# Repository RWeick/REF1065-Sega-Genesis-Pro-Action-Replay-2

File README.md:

# REF1065-Sega-Genesis-Pro-Action-Replay-2
The Kicad files and eprom dump of the Sega Genesis Pro Action Replay 2.

PCB Thickness: 1.6 mm

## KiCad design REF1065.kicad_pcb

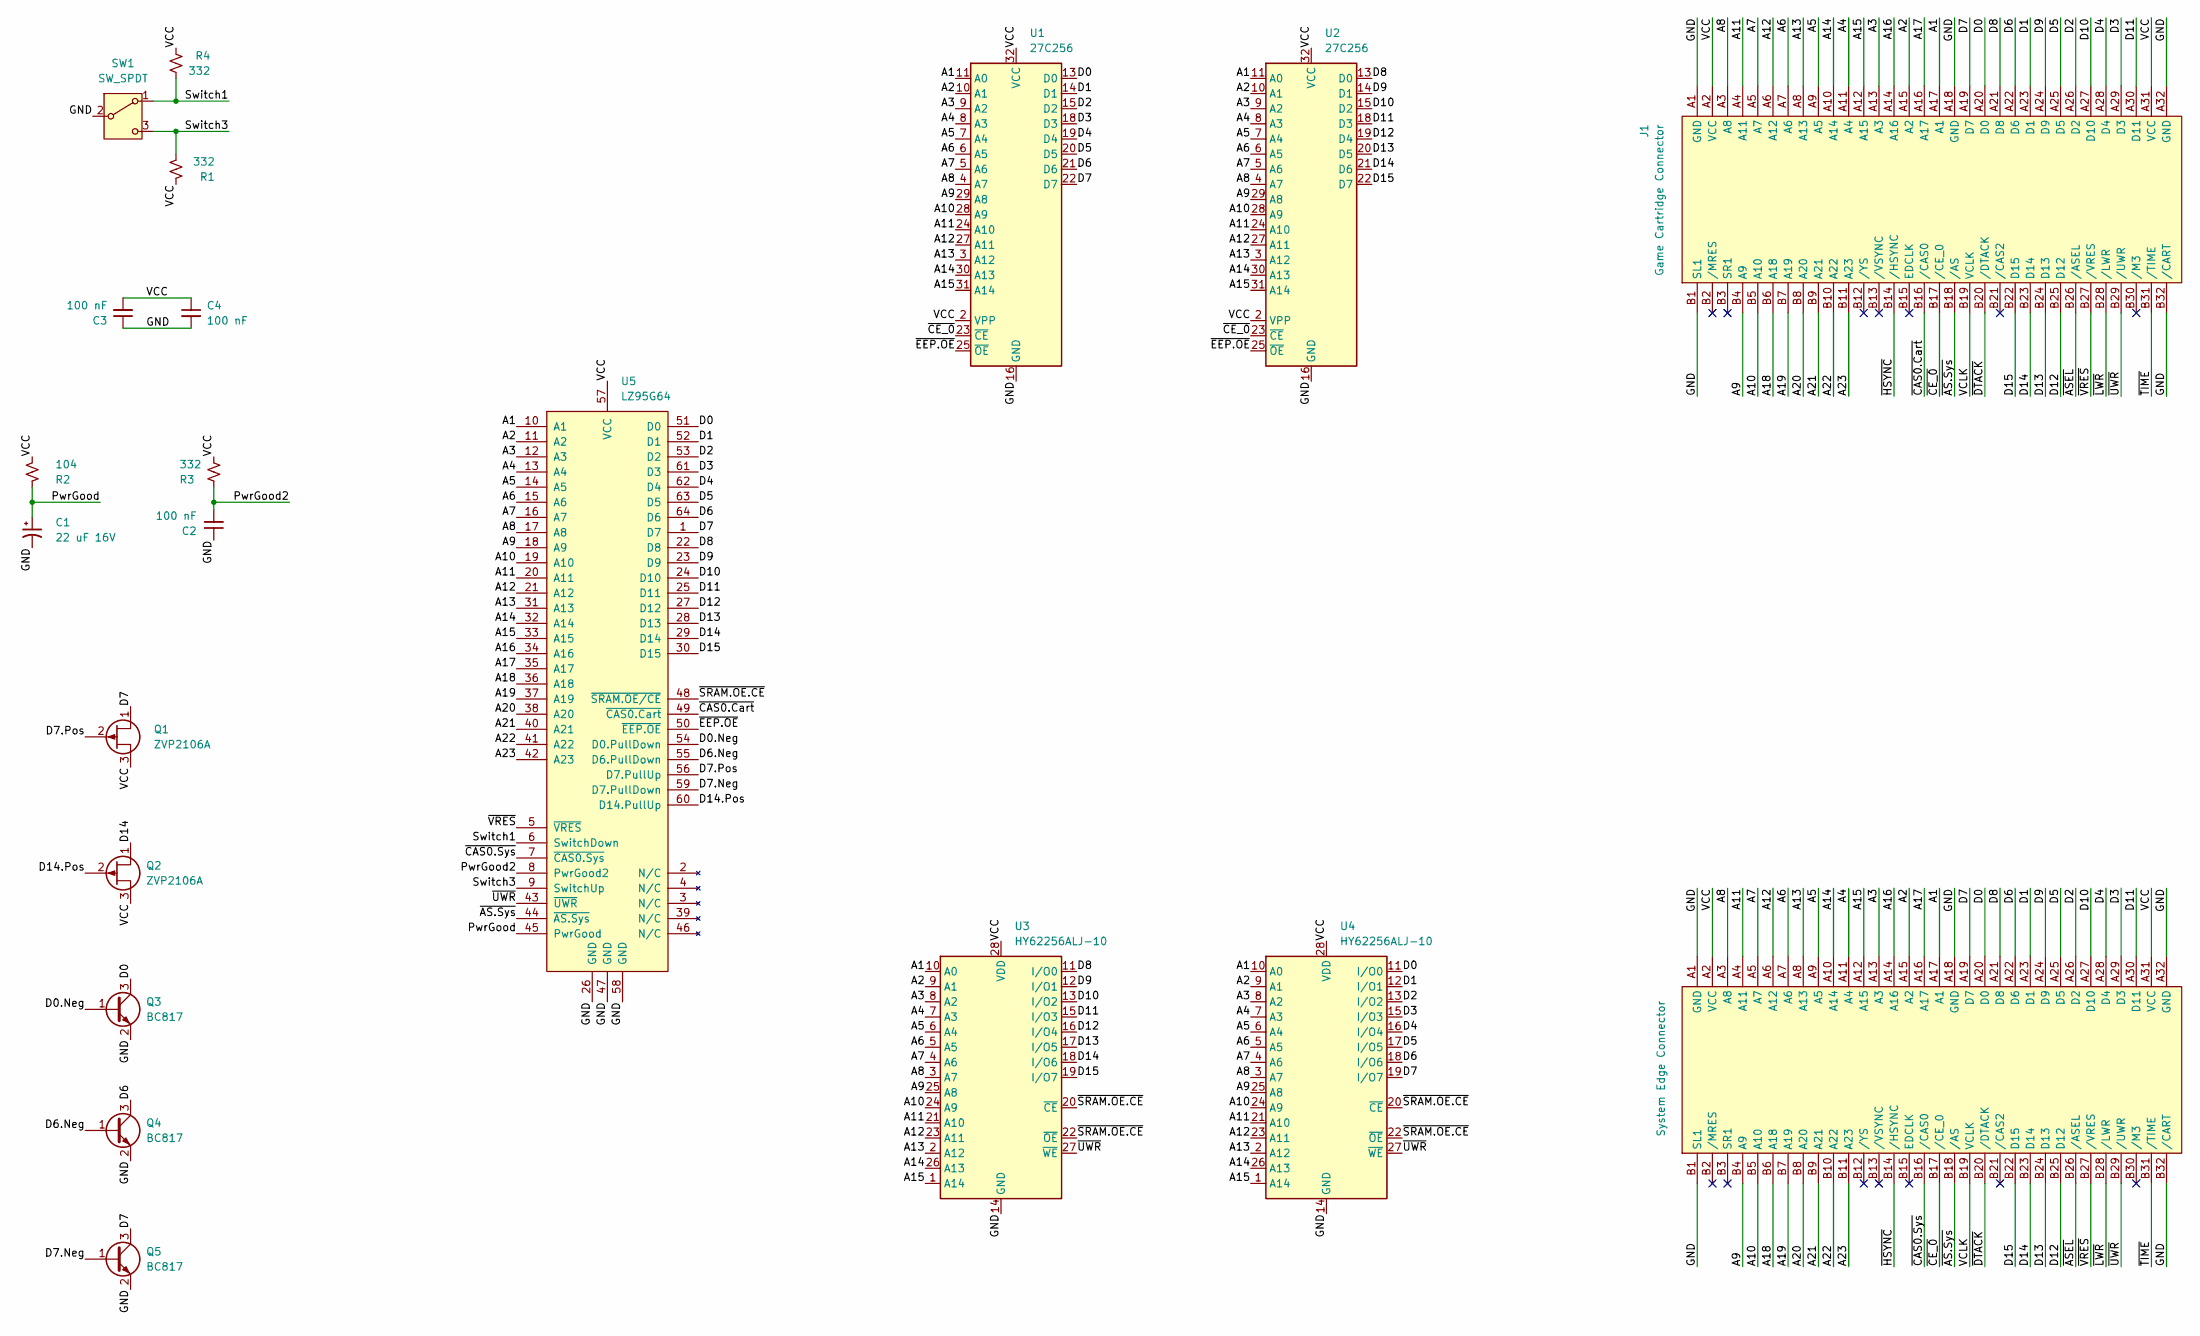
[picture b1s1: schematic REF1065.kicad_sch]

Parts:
C1: 22 uF 16V; Capacitor
C2, C3, C4: 100 nF; Capacitor
J1: Game Cartridge Connector; Upper Edge Connector
J2: System Edge Connector; Lower Edge Connector
Q1, Q2: ZVP2106A; TO-92Flat
Q3, Q4, Q5: BC817; SOT-23
R1, R3, R4: 332; Resistor
R2: 104; Resistor
SW1: SW_SPDT; Switch
U1, U2: 27C256
U3, U4: HY62256ALJ-10; HY62256ALJ
U5: LZ95G64

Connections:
/A1: J1.A17 (A1), J2.A17 (A1), U1.11 (A0), U2.11 (A0), U3.10 (A0), U4.10 (A0), U5.10 (A1)
/A2: J1.A15 (A2), J2.A15 (A2), U1.10 (A1), U2.10 (A1), U3.9 (A1), U4.9 (A1), U5.11 (A2)
/A3: J1.A13 (A3), J2.A13 (A3), U1.9 (A2), U2.9 (A2), U3.8 (A2), U4.8 (A2), U5.12 (A3)
/A4: J1.A11 (A4), J2.A11 (A4), U1.8 (A3), U2.8 (A3), U3.7 (A3), U4.7 (A3), U5.13 (A4)
/A5: J1.A9 (A5), J2.A9 (A5), U1.7 (A4), U2.7 (A4), U3.6 (A4), U4.6 (A4), U5.14 (A5)
/A6: J1.A7 (A6), J2.A7 (A6), U1.6 (A5), U2.6 (A5), U3.5 (A5), U4.5 (A5), U5.15 (A6)
/A7: J1.A5 (A7), J2.A5 (A7), U1.5 (A6), U2.5 (A6), U3.4 (A6), U4.4 (A6), U5.16 (A7)
/A8: J1.A3 (A8), J2.A3 (A8), U1.4 (A7), U2.4 (A7), U3.3 (A7), U4.3 (A7), U5.17 (A8)
/A9: J1.B4 (A9), J2.B4 (A9), U1.29 (A8), U2.29 (A8), U3.25 (A8), U4.25 (A8), U5.18 (A9)
/A10: J1.B5 (A10), J2.B5 (A10), U1.28 (A9), U2.28 (A9), U3.24 (A9), U4.24 (A9), U5.19 (A10)
/A11: J1.A4 (A11), J2.A4 (A11), U1.24 (A10), U2.24 (A10), U3.21 (A10), U4.21 (A10), U5.20 (A11)
/A12: J1.A6 (A12), J2.A6 (A12), U1.27 (A11), U2.27 (A11), U3.23 (A11), U4.23 (A11), U5.21 (A12)
/A13: J1.A8 (A13), J2.A8 (A13), U1.3 (A12), U2.3 (A12), U3.2 (A12), U4.2 (A12), U5.31 (A13)
/A14: J1.A10 (A14), J2.A10 (A14), U1.30 (A13), U2.30 (A13), U3.26 (A13), U4.26 (A13), U5.32 (A14)
/A15: J1.A12 (A15), J2.A12 (A15), U1.31 (A14), U2.31 (A14), U3.1 (A14), U4.1 (A14), U5.33 (A15)
/A16: J1.A14 (A16), J2.A14 (A16), U5.34 (A16)
/A17: J1.A16 (A17), J2.A16 (A17), U5.35 (A17)
/A18: J1.B6 (A18), J2.B6 (A18), U5.36 (A18)
/A19: J1.B7 (A19), J2.B7 (A19), U5.37 (A19)
/A20: J1.B8 (A20), J2.B8 (A20), U5.38 (A20)
/A21: J1.B9 (A21), J2.B9 (A21), U5.40 (A21)
/A22: J1.B10 (A22), J2.B10 (A22), U5.41 (A22)
/A23: J1.B11 (A23), J2.B11 (A23), U5.42 (A23)
/D0: J1.A20 (D0), J2.A20 (D0), Q3.3 (C), U1.13 (D0), U4.11 (I/O0), U5.51 (D0)
/D0.Neg: Q3.1 (B), U5.54 (D0.PullDown)
/D1: J1.A23 (D1), J2.A23 (D1), U1.14 (D1), U4.12 (I/O1), U5.52 (D1)
/D2: J1.A26 (D2), J2.A26 (D2), U1.15 (D2), U4.13 (I/O2), U5.53 (D2)
/D3: J1.A29 (D3), J2.A29 (D3), U1.18 (D3), U4.15 (I/O3), U5.61 (D3)
/D4: J1.A28 (D4), J2.A28 (D4), U1.19 (D4), U4.16 (I/O4), U5.62 (D4)
/D5: J1.A25 (D5), J2.A25 (D5), U1.20 (D5), U4.17 (I/O5), U5.63 (D5)
/D6: J1.A22 (D6), J2.A22 (D6), Q4.3 (C), U1.21 (D6), U4.18 (I/O6), U5.64 (D6)
/D6.Neg: Q4.1 (B), U5.55 (D6.PullDown)
/D7: J1.A19 (D7), J2.A19 (D7), Q1.1 (D), Q5.3 (C), U1.22 (D7), U4.19 (I/O7), U5.1 (D7)
/D7.Neg: Q5.1 (B), U5.59 (D7.PullDown)
/D7.Pos: Q1.2 (G), U5.56 (D7.PullUp)
/D8: J1.A21 (D8), J2.A21 (D8), U2.13 (D0), U3.11 (I/O0), U5.22 (D8)
/D9: J1.A24 (D9), J2.A24 (D9), U2.14 (D1), U3.12 (I/O1), U5.23 (D9)
/D10: J1.A27 (D10), J2.A27 (D10), U2.15 (D2), U3.13 (I/O2), U5.24 (D10)
/D11: J1.A30 (D11), J2.A30 (D11), U2.18 (D3), U3.15 (I/O3), U5.25 (D11)
/D12: J1.B25 (D12), J2.B25 (D12), U2.19 (D4), U3.16 (I/O4), U5.27 (D12)
/D13: J1.B24 (D13), J2.B24 (D13), U2.20 (D5), U3.17 (I/O5), U5.28 (D13)
/D14: J1.B23 (D14), J2.B23 (D14), Q2.1 (D), U2.21 (D6), U3.18 (I/O6), U5.29 (D14)
/D14.Pos: Q2.2 (G), U5.60 (D14.PullUp)
/D15: J1.B22 (D15), J2.B22 (D15), U2.22 (D7), U3.19 (I/O7), U5.30 (D15)
/GND: C1.2, C2.1, C3.1, C4.2, J1.A1 (GND), J1.A18 (GND), J1.A32 (GND), J1.B1 (SL1), J1.B32 (/CART), J2.A1 (GND), J2.A18 (GND), J2.A32 (GND), J2.B1 (SL1), J2.B32 (/CART), Q3.2 (E), Q4.2 (E), Q5.2 (E), SW1.2 (B), U1.16 (GND), U2.16 (GND), U3.14 (GND), U4.14 (GND), U5.26 (GND), U5.47 (GND), U5.58 (GND)
/PwrGood: C1.1, R2.1, U5.45 (PwrGood)
/PwrGood2: C2.2, R3.2, U5.8 (PwrGood2)
/Switch1: R4.1, SW1.1 (A), U5.6 (SwitchDown)
/Switch3: R1.1, SW1.3 (C), U5.9 (SwitchUp)
/VCC: C3.2, C4.1, J1.A2 (VCC), J1.A31 (VCC), J2.A2 (VCC), J2.A31 (VCC), Q1.3 (S), Q2.3 (S), R1.2, R2.2, R3.1, R4.2, U1.2 (VPP), U1.32 (VCC), U2.2 (VPP), U2.32 (VCC), U3.28 (VDD), U4.28 (VDD), U5.57 (VCC)
/VCLK: J1.B19 (VCLK), J2.B19 (VCLK)
/~AS.Sys: J1.B18 (/AS), J2.B18 (/AS), U5.44 (~AS.Sys)
/~ASEL: J1.B26 (/ASEL), J2.B26 (/ASEL)
/~CAS0.Cart: J1.B16 (/CAS0), U5.49 (~CAS0.Cart)
/~CAS0.Sys: J2.B16 (/CAS0), U5.7 (~CAS0.Sys)
/~CE_0: J1.B17 (/CE_0), J2.B17 (/CE_0), U1.23 (~CE), U2.23 (~CE)
/~DTACK: J1.B20 (/DTACK), J2.B20 (/DTACK)
/~EEP.OE: U1.25 (~OE), U2.25 (~OE), U5.50 (~EEP.OE)
/~HSYNC: J1.B14 (/HSYNC), J2.B14 (/HSYNC)
/~LWR: J1.B28 (/LWR), J2.B28 (/LWR)
/~SRAM.OE.CE: U3.20 (~CE), U3.22 (~OE), U4.20 (~CE), U4.22 (~OE), U5.48 (~SRAM.OE/CE)
/~TIME: J1.B31 (/TIME), J2.B31 (/TIME)
/~UWR: J1.B29 (/UWR), J2.B29 (/UWR), U3.27 (~WE), U4.27 (~WE), U5.43 (~UWR)
/~VRES: J1.B27 (/VRES), J2.B27 (/VRES), U5.5 (~VRES)

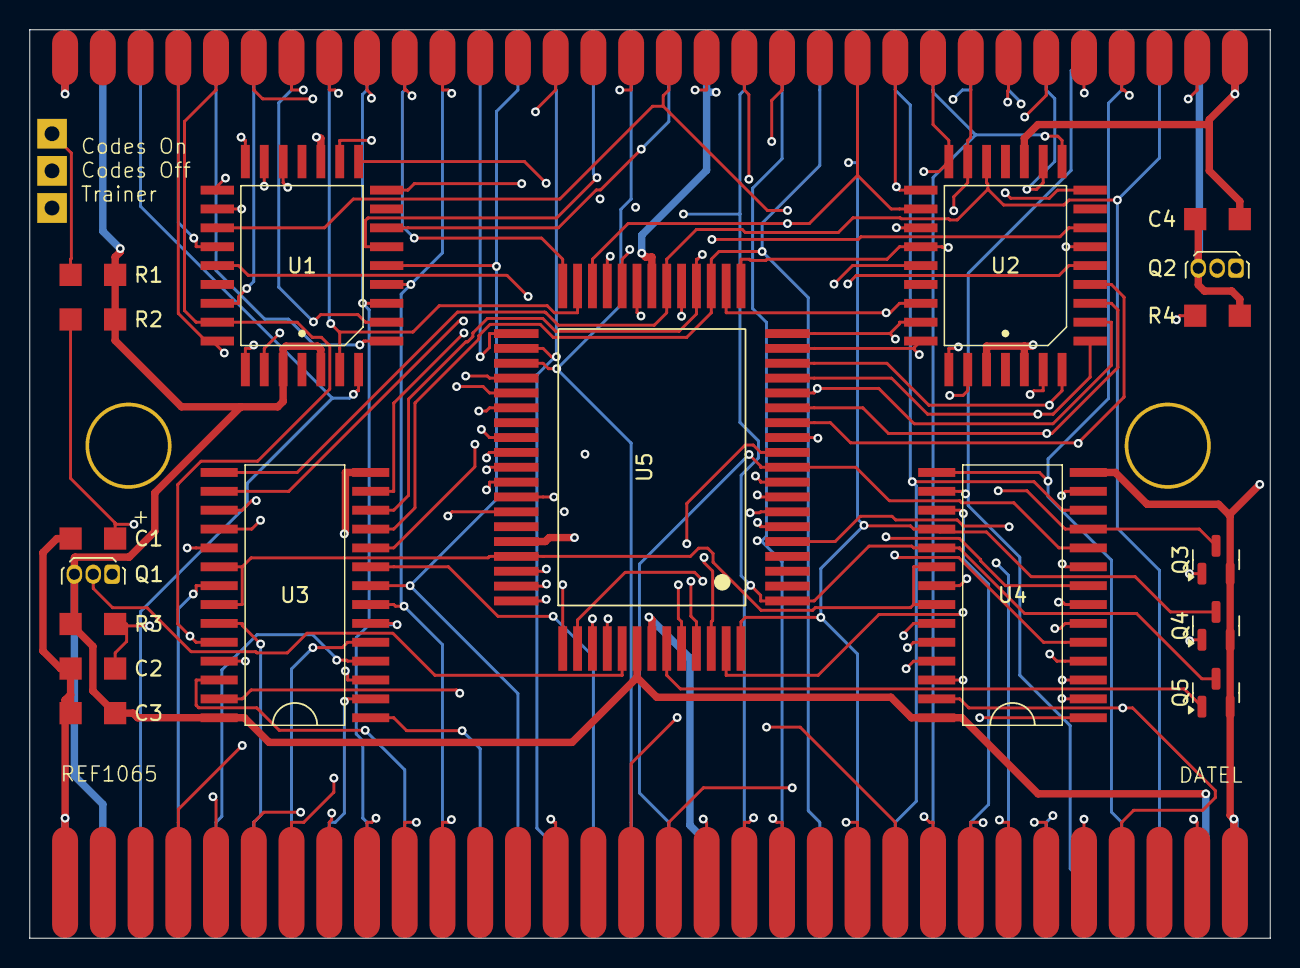
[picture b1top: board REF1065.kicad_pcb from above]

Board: 4 copper layers, 83.5 x 61.2 mm, 22 parts (0 on the bottom side), 64 nets.

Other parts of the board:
Holes: Through Holes
